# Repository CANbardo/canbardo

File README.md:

# CANbardo

CANbardo is an open hardware Universal Serial Bus (USB) to Controller
Area Network (CAN) adapter board. It is designed to be compatible with
the open source
[CANnectivity](https://github.com/CANnectivity/cannectivity) firmware.

CANbardo is licensed under the [CERN-OHL-P-2.0 license](LICENSE).

## Hardware Features

The CANbardo board provides the following features:

- Atmel SAME70N20B microcontroller
- 12 MHz 10 ppm crystal
- CAN classic support
- CAN FD (flexible data rate) support
- Fast-speed and Hi-speed USB 2.0 support (USB-C connector)
- Two independent CAN channels (DB-9M connectors)
- 2 x GPIO-controlled MCP2558FD CAN transceivers
- 2 x GPIO-controlled 120 ohm CAN bus termination resistors
- GPIO-controlled LEDs:
  - 2 x CAN channel state LEDs (green)
  - 2 x CAN channel activity LEDs (yellow)
  - 2 x CAN channel error LEDs (red)
  - 1 x Device Firmware Upgrade (DFU) LED (yellow)
- Power LED (green)
- Device Firmware Upgrade (DFU) push button
- Serial Wire Debug (SWD) and UART (3V3) available on header

## Firmware Support

The CANbardo board is supported by the following firmware:

- [Zephyr RTOS](https://docs.zephyrproject.org/latest/boards/others/canbardo/doc/index.html)
- [CANnectivity](https://github.com/CANnectivity/cannectivity)

## Enclosure

An [OpenSCAD](https://openscad.org) model for an acyllic enclosure is
available under the [Enclosure](Enclosure) folder. This model is
designed to laser cut in 2 mm clear acrylic plates and fitted to the
CANbardo board using eight M3x6 BH insex screws and four M3x8 threaded
standoffs.

## Design Documentation

The following design documentation is available:

- [Schematic](Documents/CANbardo_Schematic.pdf)
- [Layout](Documents/CANbardo-Layout.pdf)
- [3D model](Documents/CANbardo.step)
- [KiCad files](Kicad_8_files)
- [Fabrication files](Fabrication_files)
- [3D view](Documents/3D_view.png)
- [Enclosure](Enclosure)

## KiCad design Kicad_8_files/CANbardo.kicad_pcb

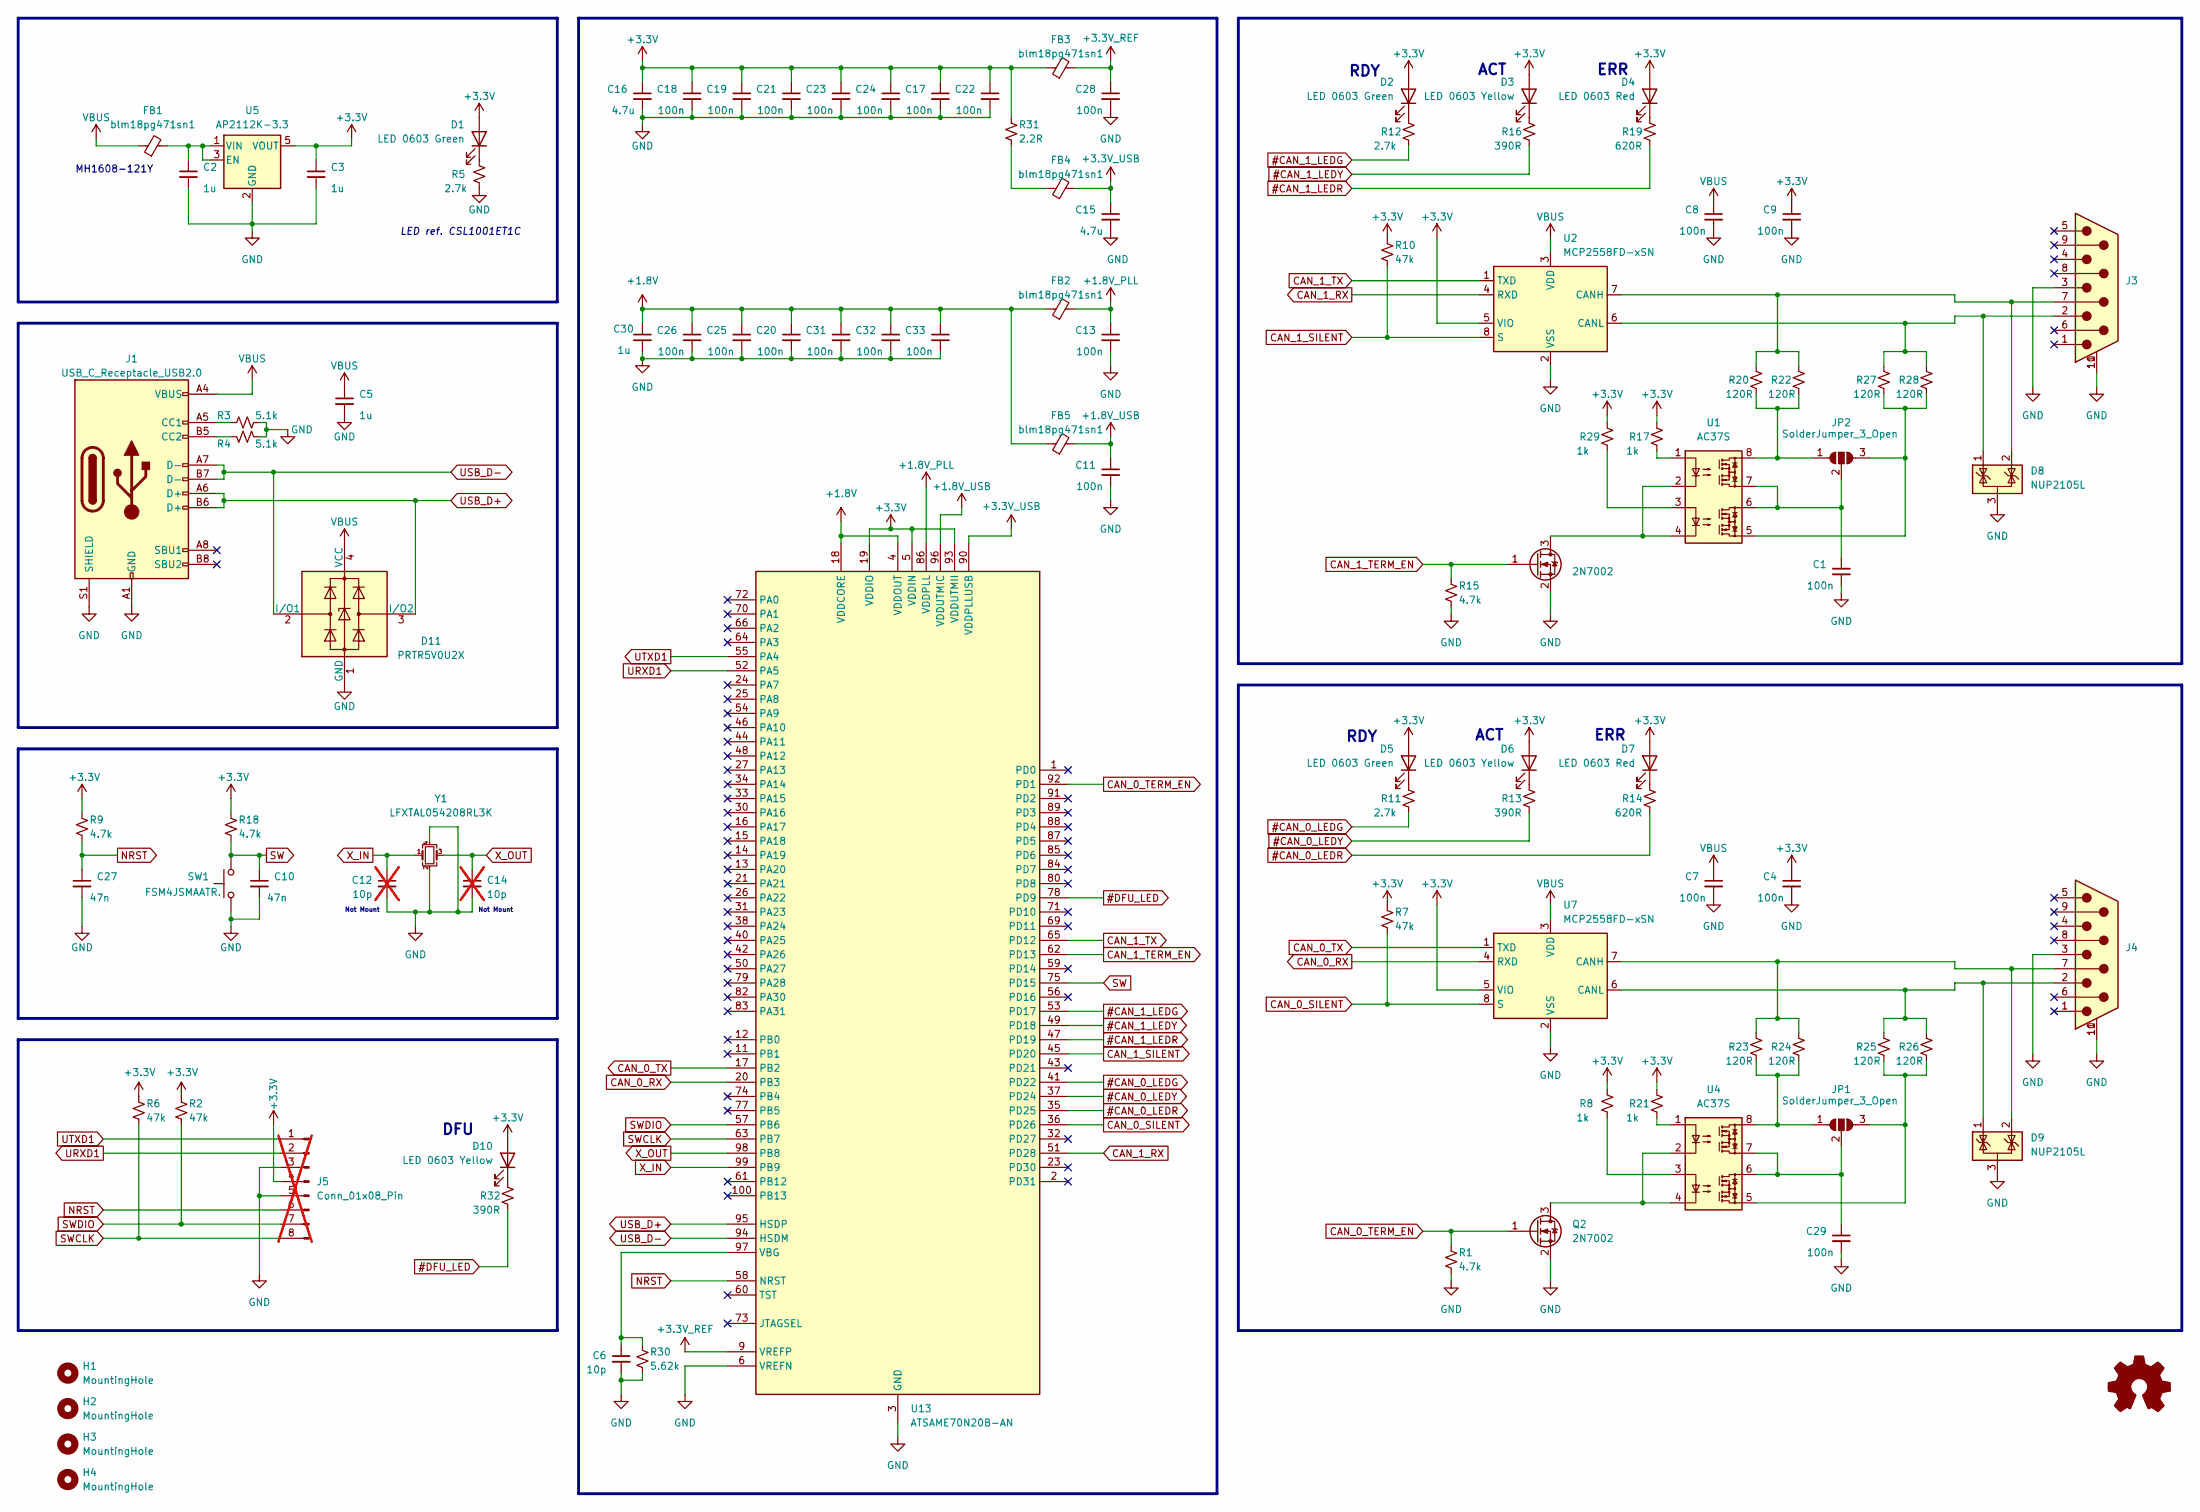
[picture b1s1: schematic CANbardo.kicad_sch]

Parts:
C1, C4, C7, C8, C9, C11, C13, C17, C18, C19, C20, C21, C22, C23, C24, C25, C26, C28, C29, C31, C32, C33: 100n; C_0603_1608Metric
C2, C3, C5, C30: 1u; C_0805_2012Metric
C6: 10p; C_0603_1608Metric
C10, C27: 47n; C_0603_1608Metric
C12, C14: 10p; C_0603_1608Metric; not fitted
C15, C16: 4.7u; C_0805_2012Metric
D1, D2, D5: LED 0603 Green; LED_0603_1608Metric
D3, D6, D10: LED 0603 Yellow; LED_0603_1608Metric
D4, D7: LED 0603 Red; LED_0603_1608Metric
D8, D9: NUP2105L; SOT-23
D11: PRTR5V0U2X; SOT-143
FB1, FB2, FB3, FB4, FB5: blm18pg471sn1; L_0603_1608Metric
H1, H2, H3, H4: MountingHole; MountingHole_3.5mm
J1: USB_C_Receptacle_USB2.0; USB_C_Receptacle_GCT_USB4105-xx-A_16P_TopMnt_Horizontal
J3, J4: DE9_Plug_MountingHoles; CONN9_5747840-4_TEC
J5: Conn_01x08_Pin; PinHeader_1x08_P2.54mm_Vertical_zigzag; not fitted
JP1, JP2: SolderJumper_3_Open; SolderJumper-3_P2.0mm_Open_TrianglePad1.0x1.5mm
LOGO1: Logo_Open_Hardware_Small; OSHW-Symbol_8.9x8mm_SilkScreen
Q1, Q2: 2N7002; SOT-23
R1, R9, R15, R18: 4.7k; R_0603_1608Metric
R2, R6, R7, R10: 47k; R_0603_1608Metric
R3, R4: 5.1k; R_0603_1608Metric
R5, R11, R12: 2.7k; R_0603_1608Metric
R8, R17, R21, R29: 1k; R_0603_1608Metric
R13, R16, R32: 390R; R_0603_1608Metric
R14, R19: 620R; R_0603_1608Metric
R20, R22, R23, R24, R25, R26, R27, R28: 120R; R_0603_1608Metric
R30: 5.62k; R_0603_1608Metric
R31: 2.2R; R_0603_1608Metric
SW1: FSM4JSMAATR.; SW_SMD_Tactile_4pin
U1, U4: AC37S; SOP-8GW_4.4x9.4mm_P2.54mm
U2, U7: MCP2558FD-xSN; SOIC-8_3.9x4.9mm_P1.27mm
U5: AP2112K-3.3; SOT-23-5
U13: ATSAME70N20B-AN; LQFP-100_14x14mm_P0.5mm
Y1: LFXTAL054208RL3K; Crystal_SMD_3225-4Pin_3.2x2.5mm_HandSoldering

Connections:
#CAN_0_LEDG: R11.2, U13.41 (PD22)
#CAN_0_LEDR: R14.2, U13.35 (PD25)
#CAN_0_LEDY: R13.2, U13.37 (PD24)
#CAN_1_LEDG: R12.2, U13.53 (PD17)
#CAN_1_LEDR: R19.2, U13.47 (PD19)
#CAN_1_LEDY: R16.2, U13.49 (PD18)
#DFU_LED: R32.2, U13.78 (PD9)
+1.8V: C20.1, C25.1, C26.1, C30.1, C31.1, C32.1, C33.1, FB2.1, FB5.1, U13.4 (VDDOUT), U13.18 (VDDCORE), U13.22 (VDDCORE), U13.39 (VDDCORE), U13.76 (VDDCORE)
+1.8V_PLL: C13.1, FB2.2, U13.86 (VDDPLL)
+1.8V_USB: C11.1, FB5.2, U13.96 (VDDUTMIC)
+3.3V: C3.1, C4.1, C9.1, C16.1, C17.1, C18.1, C19.1, C21.1, C22.1, C23.1, C24.1, D1.2 (A), D2.2 (A), D3.2 (A), D4.2 (A), D5.2 (A), D6.2 (A), D7.2 (A), D10.2 (A), FB3.1, J5.4, R2.1, R6.1, R7.1, R8.1, R9.1, R10.1, R17.1, R18.1, R21.1, R29.1, R31.1, U2.5 (VIO), U5.5 (VOUT), U7.5 (VIO), U13.5 (VDDIN), U13.19 (VDDIO), U13.28 (VDDIO), U13.68 (VDDIO), U13.81 (VDDIO), U13.93 (VDDUTMII)
+3.3V_REF: C28.1, FB3.2, U13.9 (VREFP)
+3.3V_USB: C15.1, FB4.2, U13.90 (VDDPLLUSB)
CAN_0_RX: U7.4 (RXD), U13.20 (PB3)
CAN_0_SILENT: R7.2, U7.8 (S), U13.36 (PD26)
CAN_0_TERM_EN: Q2.1 (G), R1.1, U13.92 (PD1)
CAN_0_TX: U7.1 (TXD), U13.17 (PB2)
CAN_1_RX: U2.4 (RXD), U13.51 (PD28)
CAN_1_SILENT: R10.2, U2.8 (S), U13.45 (PD20)
CAN_1_TERM_EN: Q1.1 (G), R15.1, U13.62 (PD13)
CAN_1_TX: U2.1 (TXD), U13.65 (PD12)
GND: C1.2, C2.2, C3.2, C4.2, C5.2, C6.2, C7.2, C8.2, C9.2, C10.2, C11.2, C12.2, C13.2, C14.2, C15.2, C16.2, C17.2, C18.2, C19.2, C20.2, C21.2, C22.2, C23.2, C24.2, C25.2, C26.2, C27.2, C28.2, C29.2, C30.2, C31.2, C32.2, C33.2, D8.3 (A), D9.3 (A), D11.1 (GND), J1.A1 (GND), J1.A12 (GND), J1.B1 (GND), J1.B12 (GND), J1.S1 (SHIELD), J3.3, J3.10 (PAD), J3.11 (PAD), J4.3, J4.10 (PAD), J4.11 (PAD), J5.3, J5.5, Q1.2 (S), Q2.2 (S), R1.2, R3.2, R4.2, R5.2, R15.2, R30.2, SW1.1, U2.2 (VSS), U5.2 (GND), U7.2 (VSS), U13.3 (GND), U13.6 (VREFN), U13.7 (GND), U13.8 (GND), U13.10 (GND), U13.29 (GND), U13.67 (GND), Y1.2, Y1.4
NRST: C27.1, J5.6, R9.2, U13.58 (NRST)
unnamed: D1.1 (K), R5.1
unnamed: D2.1 (K), R12.1
unnamed: D3.1 (K), R16.1
unnamed: D4.1 (K), R19.1
unnamed: D5.1 (K), R11.1
unnamed: D6.1 (K), R13.1
unnamed: D7.1 (K), R14.1
unnamed: D10.1 (K), R32.1
unnamed: FB4.1, R31.2
unnamed: J1.A5 (CC1), R3.1
unnamed: J1.B5 (CC2), R4.1
unnamed: JP1.1 (A), R23.2, R24.2, U4.8
unnamed: JP1.3 (B), R25.2, R26.2, U4.5
unnamed: C29.1, JP1.2 (C), U4.6, U4.7
unnamed: JP2.1 (A), R20.2, R22.2, U1.8
unnamed: JP2.3 (B), R27.2, R28.2, U1.5
unnamed: C1.1, JP2.2 (C), U1.6, U1.7
unnamed: Q1.3 (D), U1.2, U1.4
unnamed: Q2.3 (D), U4.2, U4.4
unnamed: R8.2, U4.3
unnamed: R17.2, U1.1
unnamed: R21.2, U4.1
unnamed: R29.2, U1.3
unnamed: D8.2 (K), J3.7, R20.1, R22.1, U2.7 (CANH)
unnamed: D8.1 (K), J3.2, R27.1, R28.1, U2.6 (CANL)
unnamed: C2.1, FB1.2, U5.1 (VIN), U5.3 (EN)
unnamed: D9.2 (K), J4.7, R23.1, R24.1, U7.7 (CANH)
unnamed: D9.1 (K), J4.2, R25.1, R26.1, U7.6 (CANL)
unnamed: C6.1, R30.1, U13.97 (VBG)
SW: C10.1, R18.2, SW1.2, U13.75 (PD15)
SWCLK: J5.8, R6.2, U13.63 (PB7)
SWDIO: J5.7, R2.2, U13.57 (PB6)
URXD1: J5.2, U13.52 (PA5)
USB_D+: D11.3 (I/O2), J1.A6 (D+), J1.B6 (D+), U13.95 (HSDP)
USB_D-: D11.2 (I/O1), J1.A7 (D-), J1.B7 (D-), U13.94 (HSDM)
UTXD1: J5.1, U13.55 (PA4)
VBUS: C5.1, C7.1, C8.1, D11.4 (VCC), FB1.1, J1.A4 (VBUS), J1.A9 (VBUS), J1.B4 (VBUS), J1.B9 (VBUS), U2.3 (VDD), U7.3 (VDD)
X_IN: C12.1, U13.99 (PB9), Y1.1
X_OUT: C14.1, U13.98 (PB8), Y1.3

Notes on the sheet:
LED ref. CSL1001ET1C
ACT
MH1608-121Y
RDY
Not Mount
DFU
ERR

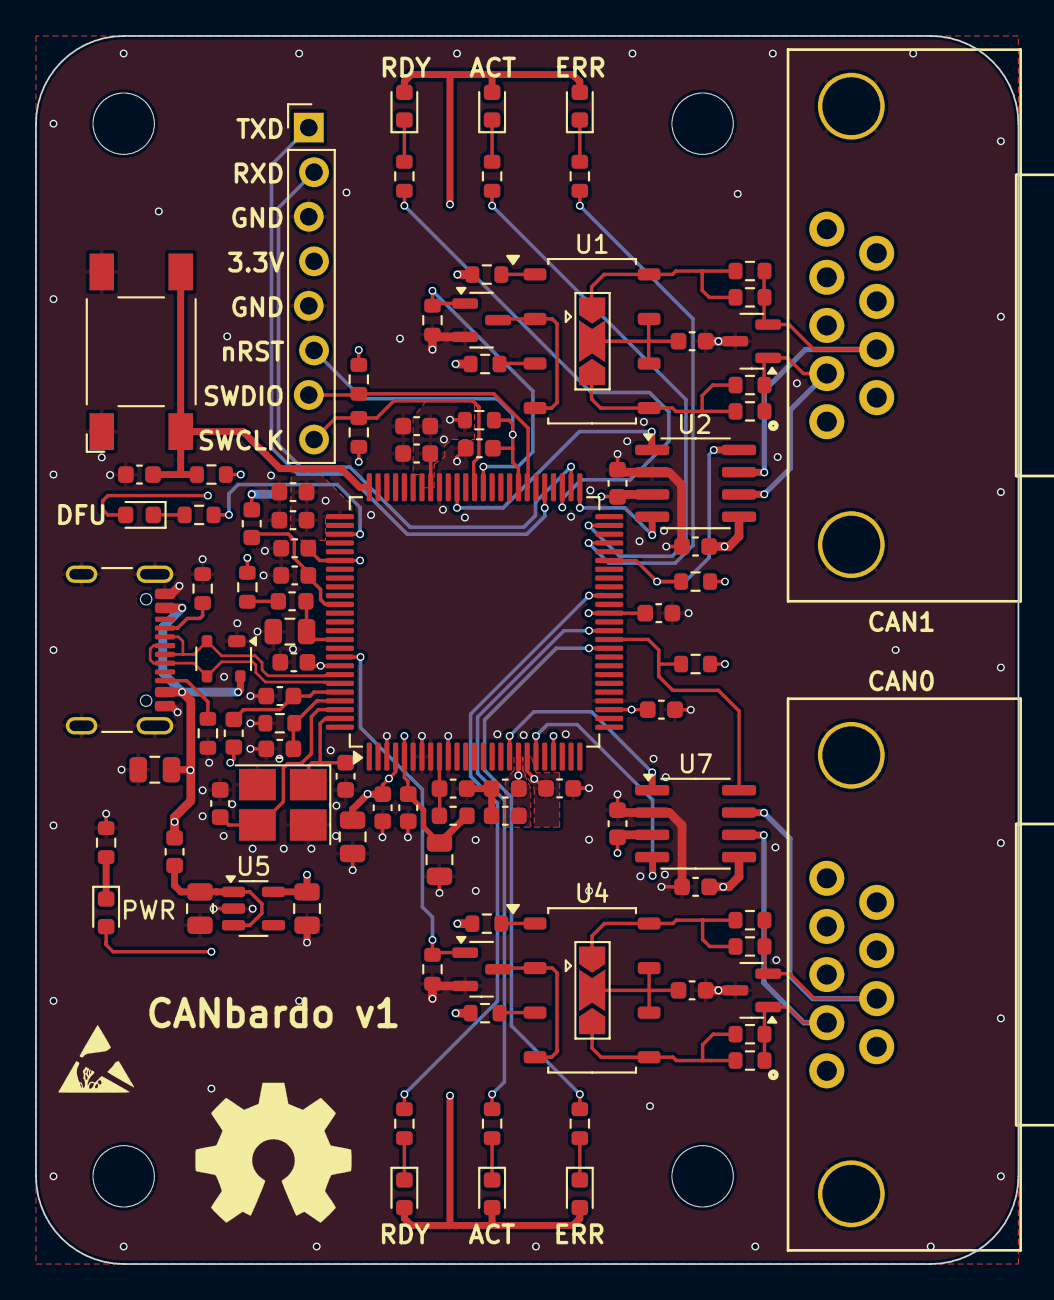
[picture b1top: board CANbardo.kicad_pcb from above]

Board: 4 copper layers, 56.0 x 70.0 mm, 102 parts (0 on the bottom side), 62 nets.

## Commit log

2024-10-27 Project v1
    Project upload
    Released version - v1
2024-10-27 README: add project description
    Add project description README file.
2025-01-06 README: replace 3D view with photo of actual board
2025-01-10 README: add links to documentation on supporting firmware
2025-08-16 enclosure: add OpenSCAD model for an acrylic enclosure
    Add an OpenSCAD model (and DXF export) for a simple acrylic enclosure.
2025-08-17 Updated LED resistors
    LED resistors updated to match intensity.
    Version updated from 1.0 to 1.1

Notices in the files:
Kicad_8_files/CANbardo.kicad_sch:
Licensed under CERN-OHL-P v2
